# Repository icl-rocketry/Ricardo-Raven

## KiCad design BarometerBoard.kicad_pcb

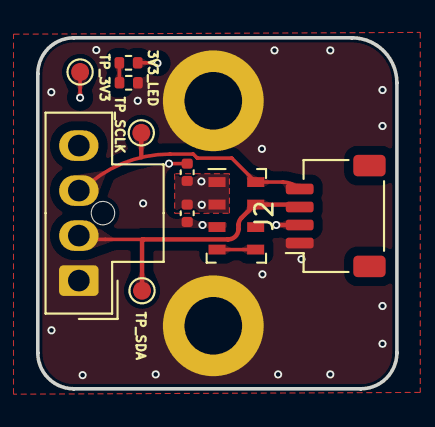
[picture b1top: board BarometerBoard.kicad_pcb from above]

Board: 4 copper layers, 19.9 x 19.5 mm, 12 parts (0 on the bottom side), 5 nets.

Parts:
3V3LED1: BLUE_LED; R_0402_1005Metric
C12, C18: 100nF; C_0402_1005Metric
H1, H4: MountingHole_Pad; MountingHole_3.2mm_M3_DIN965_Pad
J1: Conn_01x04_Pin; Molex_Nano-Fit_105309-xx04_1x04_P2.50mm_Vertical
J2: Conn_01x04_Pin; JST_SH_SM04B-SRSS-TB_1x04-1MP_P1.00mm_Horizontal
R1: 470; R_0402_1005Metric
TP1, TP2, TP3: TestPoint; TestPoint_Pad_D1.0mm
U6: MS5611-01BA; LGA-8_3x5mm_P1.25mm

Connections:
+3V3: C12.1, C18.1, J1.4, J2.2, R1.2, TP1.1, U6.1 (VDD), U6.2 (PS)
/SCLK: J1.3, J2.4, TP3.1, U6.8 (SCLK)
/SDA: J1.2, J2.3, TP2.1, U6.7 (SDI/SDA)
GND: 3V3LED1.1 (K), C12.2, C18.2, H1.1, H4.1, J1.1, J2.1, U6.3 (GND)
unnamed: 3V3LED1.2 (A), R1.1
